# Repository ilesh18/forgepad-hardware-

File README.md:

<p>
<b>Hey, I’m building HackPad!</b><br><br>
I’m designing and building a custom macro keyboard from scratch.<br>
HackPad is a 9-key programmable keypad powered by RP2040 and KMK firmware.<br>
Everything — schematic, PCB, enclosure, and firmware — is built by me.<br>
This project is about learning real hardware design and firmware not tutorials.<br><br>
I’m building HackPad to move beyond frontend-only projects.<br>
To understand embedded systems, USB HID, and PCB design properly.<br>
To ship a real physical product that actually works.<br><br>
<b>What HackPad is</b><br>
A compact, programmable macro keypad.<br>
Built for coding shortcuts, workflows, and automation.<br>
Plug & play as a USB keyboard.<br>
Fully reconfigurable using Python (KMK firmware).<br><br>
<b>components used </b><br>
RP2040 (Seeed Studio XIAO RP2040)<br>
9 Switches - Cherry MX Compatible Mechanical Switches (3×3 layout)<br>
3 RGB LEDs - SK6812MINI (3535) Addressable RGB LEDs LEDs<br>
Custom PCB<br>
Custom enclosure<br>
CircuitPython + KMK firmware<br><br>
<b>Why built this</b><br>
To learn embedded systems properly<br>
To build real hardware, not simulations<br>
To understand firmware + USB HID<br>
To move beyond frontend-only projects<br><br>

</p>

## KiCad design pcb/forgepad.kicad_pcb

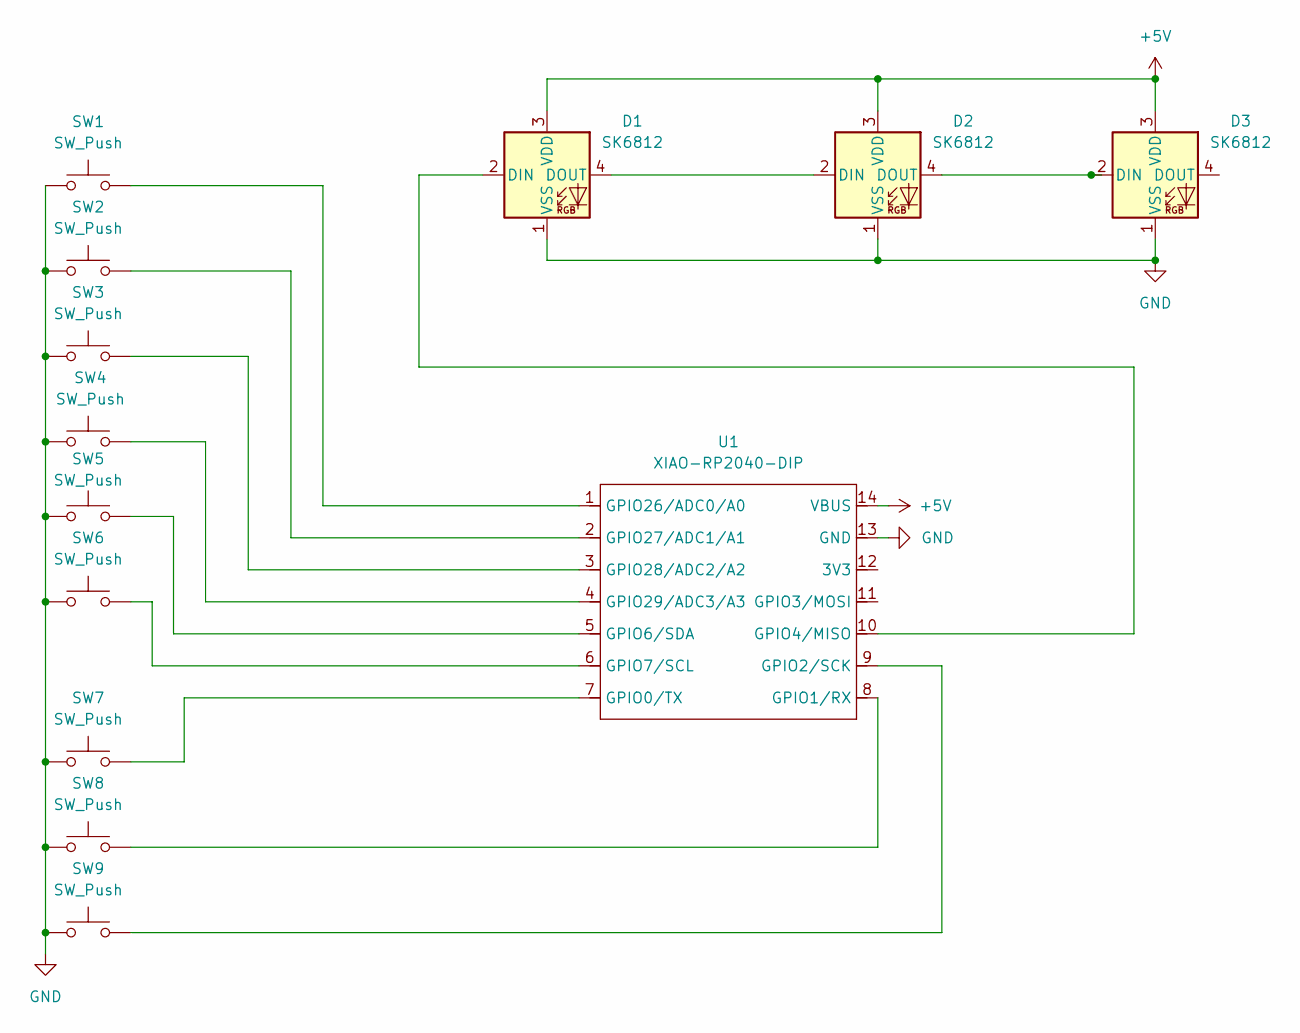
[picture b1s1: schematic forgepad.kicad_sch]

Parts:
D1, D2, D3: SK6812; LED_SK6812MINI_PLCC4_3.5x3.5mm_P1.75mm
SW1, SW2, SW3, SW4, SW5, SW6, SW7, SW8, SW9: SW_Push; SW_Cherry_MX_1.00u_PCB
U1: XIAO-RP2040-DIP

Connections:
+5V: D1.3 (VDD), D2.3 (VDD), D3.3 (VDD), U1.14 (VBUS)
GND: D1.1 (VSS), D2.1 (VSS), D3.1 (VSS), SW1.1, SW2.1, SW3.1, SW4.1, SW5.1, SW6.1, SW7.1, SW8.1, SW9.1, U1.13 (GND)
unnamed: D1.2 (DIN), U1.10 (GPIO4/MISO)
unnamed: D1.4 (DOUT), D2.2 (DIN)
unnamed: D2.4 (DOUT), D3.2 (DIN)
unnamed: SW7.2, U1.7 (GPIO0/TX)
unnamed: SW8.2, U1.8 (GPIO1/RX)
unnamed: SW9.2, U1.9 (GPIO2/SCK)
unnamed: SW5.2, U1.5 (GPIO6/SDA)
unnamed: SW6.2, U1.6 (GPIO7/SCL)
unnamed: SW1.2, U1.1 (GPIO26/ADC0/A0)
unnamed: SW2.2, U1.2 (GPIO27/ADC1/A1)
unnamed: SW3.2, U1.3 (GPIO28/ADC2/A2)
unnamed: SW4.2, U1.4 (GPIO29/ADC3/A3)

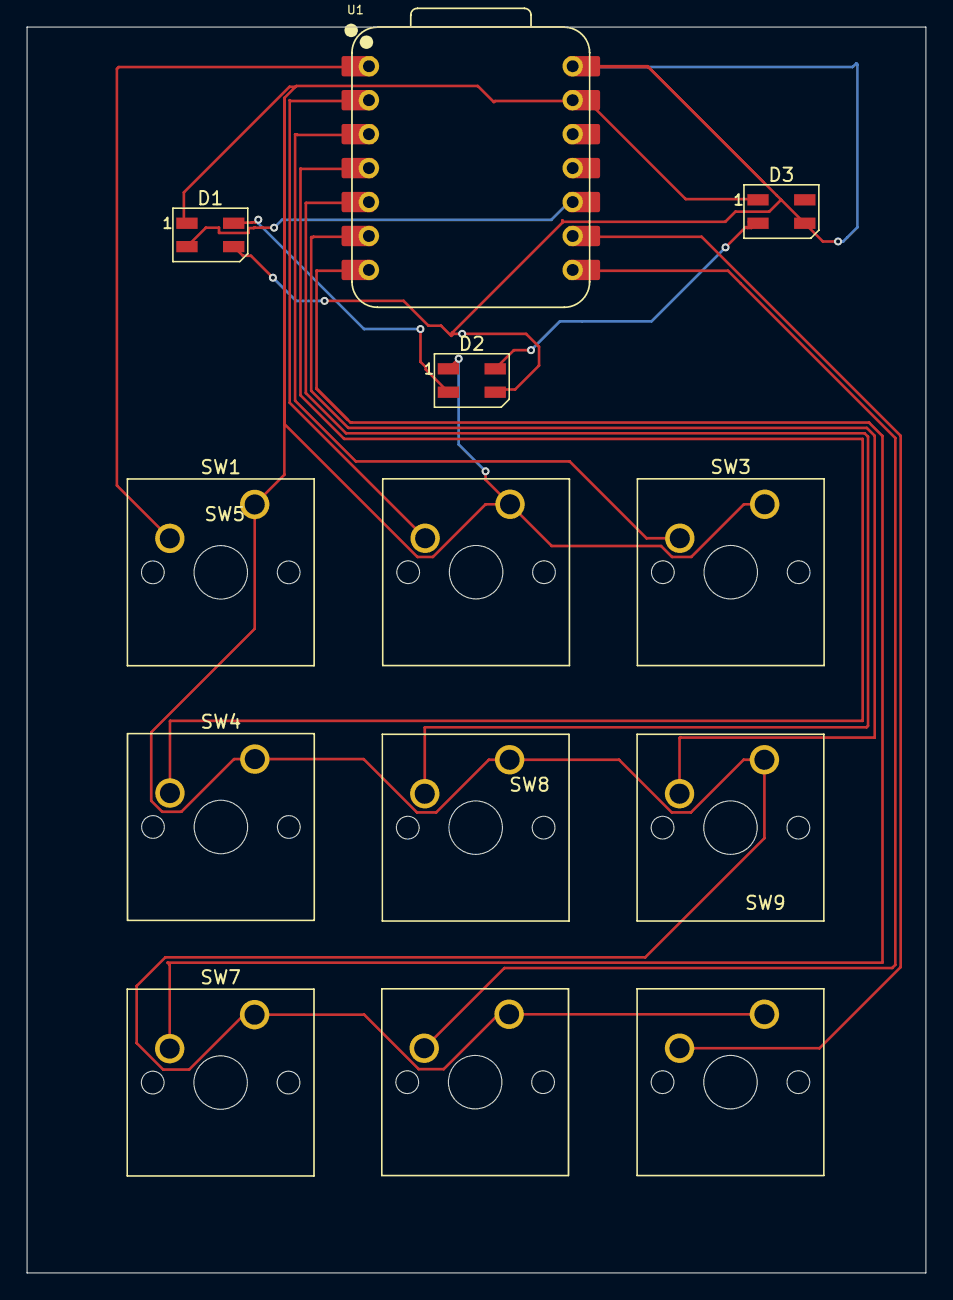
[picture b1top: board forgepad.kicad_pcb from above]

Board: 2 copper layers, 67.2 x 93.2 mm, 13 parts (0 on the bottom side), 14 nets.
